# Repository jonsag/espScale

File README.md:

# espScale

A NodeMCU measuring weight with loadcells

## Setup

Instructions at [https://how2electronics.com/iot-weighing-scale-hx711-load-cell-esp8266/](https://how2electronics.com/iot-weighing-scale-hx711-load-cell-esp8266/)  

Connect four load cells to one amplifier: [https://circuitjournal.com/50kg-load-cells-with-HX711](https://circuitjournal.com/50kg-load-cells-with-HX711)  

Blynk instructions at [https://blynk.io/en/getting-started](https://blynk.io/en/getting-started)  

## Misc

I2C addresses:  
HX711 module: n/a  
LCD screen: 0x27  

Blynk [github](https://github.com/blynkkk/blynk-library)

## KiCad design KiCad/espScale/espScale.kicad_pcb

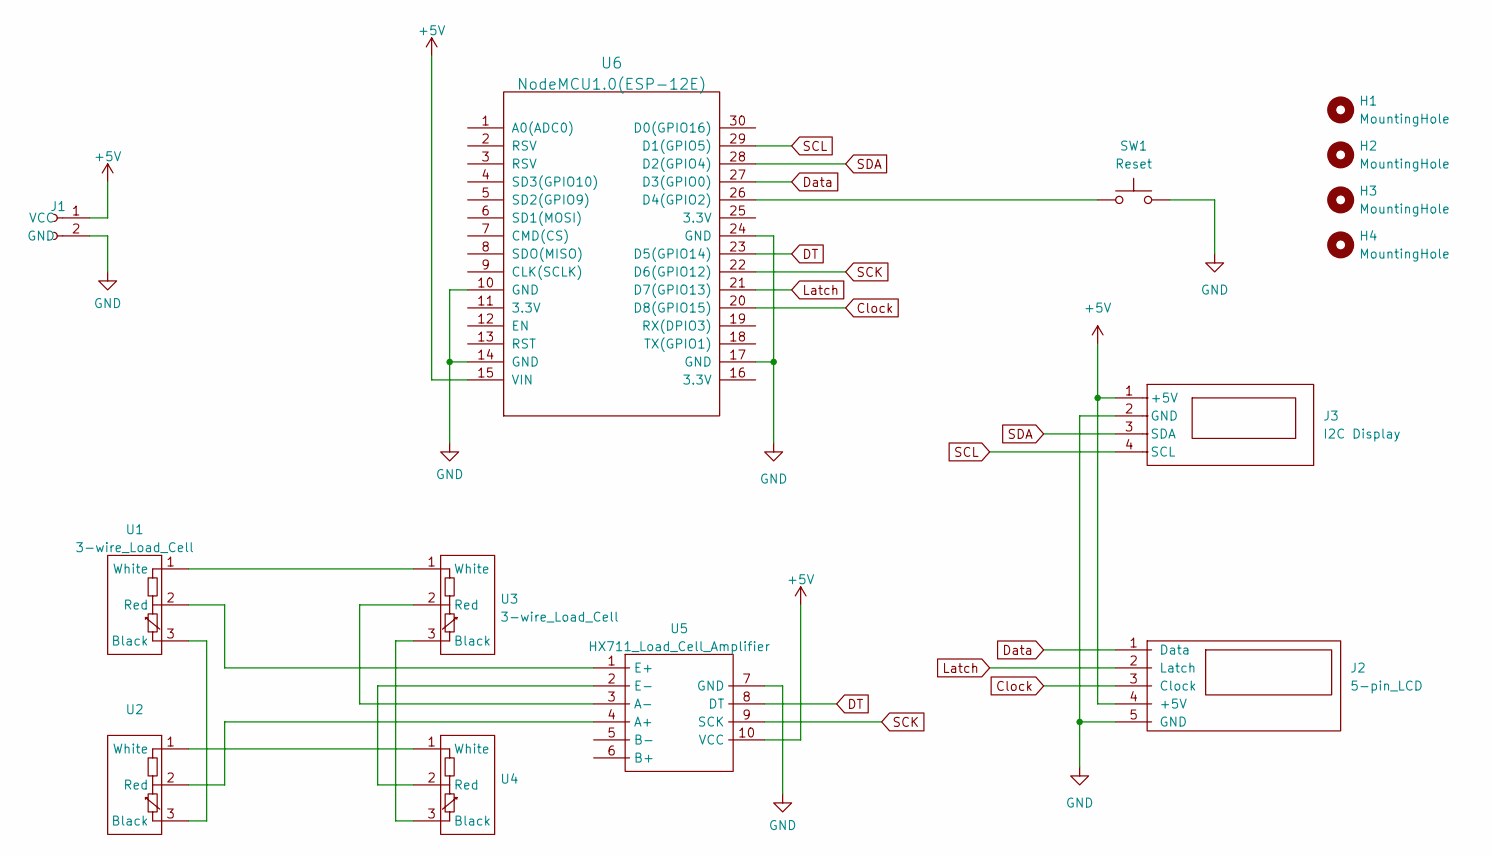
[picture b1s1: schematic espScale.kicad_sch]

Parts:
H1, H2, H3, H4: MountingHole; MountingHole_3.2mm_M3
J1: 2-pin_power_input_header
J2: 5-pin_LCD; 5-pin JST LiquidCrystal595
J3: I2C Display; 4-pin JST LCD
SW1: Reset; SW_PUSH_6mm_large
U1, U3: 3-wire_Load_Cell; 3-pin JST load cell
U2, U4: 3-pin JST load cell
U5: HX711_Load_Cell_Amplifier; HX711 Load Cell Amplifier w_pinsockets_large
U6: NodeMCU1.0(ESP-12E); NodeMCU-LoLinV3_w_pinsockets_large

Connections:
+5V: J1.1 (VCC), J2.4 (+5V), J3.1 (+5V), U5.10 (VCC), U6.15 (VIN)
Clock: J2.3 (Clock), U6.20 (D8(GPIO15))
DT: U5.8 (DT), U6.23 (D5(GPIO14))
Data: J2.1 (Data), U6.27 (D3(GPIO0))
GND: J1.2 (GND), J2.5 (GND), J3.2 (GND), SW1.2, U5.7 (GND), U6.10 (GND), U6.14 (GND), U6.17 (GND), U6.24 (GND)
Latch: J2.2 (Latch), U6.21 (D7(GPIO13))
unnamed: U1.1 (White), U3.1 (White)
unnamed: U1.2 (Red), U5.1 (E+)
unnamed: U1.3 (Black), U2.3 (Black)
unnamed: U2.1 (White), U4.1 (White)
unnamed: U2.2 (Red), U5.4 (A+)
unnamed: U3.2 (Red), U5.3 (A-)
unnamed: U3.3 (Black), U4.3 (Black)
unnamed: U4.2 (Red), U5.2 (E-)
unnamed: SW1.1, U6.26 (D4(GPIO2))
SCK: U5.9 (SCK), U6.22 (D6(GPIO12))
SCL: J3.4 (SCL), U6.29 (D1(GPIO5))
SDA: J3.3 (SDA), U6.28 (D2(GPIO4))

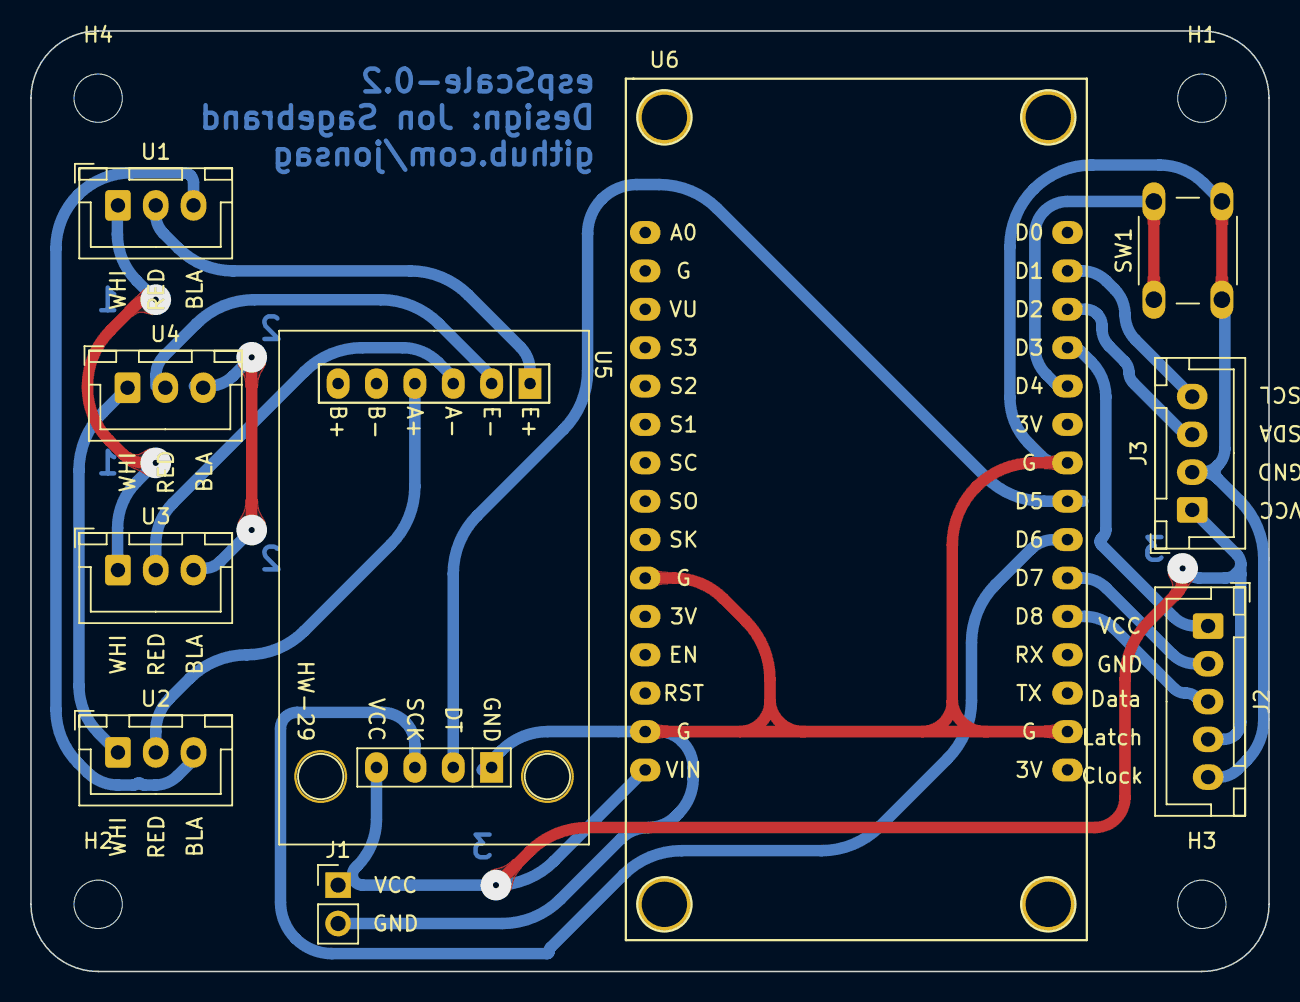
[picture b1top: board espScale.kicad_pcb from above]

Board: 2 copper layers, 81.9 x 62.2 mm, 14 parts (0 on the bottom side), 18 nets.

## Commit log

2021-03-11 test sketches
2021-03-11 blynkscale
2022-03-22 PIO conversion
2022-05-14 kicad
2022-09-18 kicad page settings
2022-10-25 new PCB, added 3-pin LCD
2023-05-14 kicad 7
